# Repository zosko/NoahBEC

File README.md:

# NoahBEC
Buck convertor 12V to 5V 3A for servos.

## Scheme

Board | Preview 
-----|-----
|

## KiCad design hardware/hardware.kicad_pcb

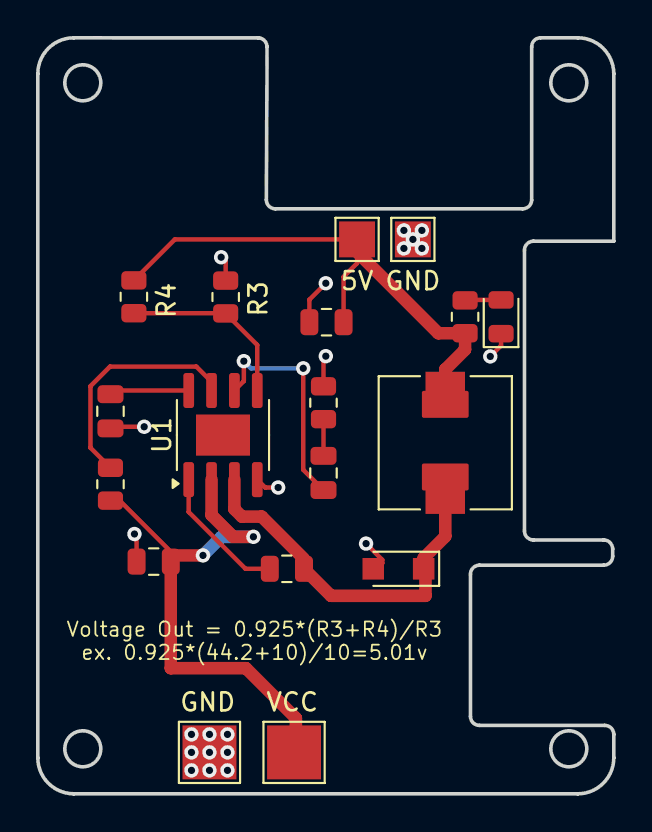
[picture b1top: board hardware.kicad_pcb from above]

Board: 2 copper layers, 32.0 x 42.0 mm, 18 parts (0 on the bottom side), 11 nets.

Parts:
5V: 5V OUTPUT; TestPoint_Pad_2.0x2.0mm
C1: 100nF; C_0805_2012Metric
C2: 3.9nF; C_0805_2012Metric
C4: 10nF; C_0805_2012Metric
C5, C6: 22uF; C_0805_2012Metric
D1: SS34; Nexperia_CFP3_SOD-123W
D2: LED; LED_0805_2012Metric
GND: GND; TestPoint_Pad_3.0x3.0mm
GND#2: GND OUTPUT; TestPoint_Pad_2.0x2.0mm
L1: 10uH; L_7.3x7.3_H3.5
R1: 6.8K; R_0805_2012Metric
R2: 100K; R_0805_2012Metric
R3: 10K; R_0805_2012Metric
R4: 44.2K; R_0805_2012Metric
R5: 300; R_0805_2012Metric
U1: MP2303ADN; SOIC-8-1EP_3.9x4.9mm_P1.27mm_EP2.29x3mm
VCC: VCC; TestPoint_Pad_3.0x3.0mm

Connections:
5V: 5V.1, C5.2, L1.1, R4.1, R5.2
GND: C1.1, C5.1, C6.1, D1.2 (A), D2.1 (K), GND.1, GND#2.1, R1.1, R3.1, U1.4 (GND)
unnamed: C2.1, R1.2
unnamed: C4.1, D1.1 (K), L1.2, U1.3 (SW)
unnamed: D2.2 (A), R5.1
unnamed: C6.2, R2.1, U1.2 (IN), VCC.1
unnamed: C4.2, U1.1 (BS)
unnamed: C2.2, U1.6 (COMP)
unnamed: R2.2, U1.7 (EN)
unnamed: R3.2, R4.2, U1.5 (FB)
unnamed: C1.2, U1.8 (SS)

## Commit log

2022-12-12 improve version
2022-12-19 rev1
2023-11-30 remove old project
2023-11-30 add noah bec rev 1
2023-11-30 add new images
2023-12-04 add 3d model for inductor
2023-12-04 replace pcb image
2024-03-05 rev1 project
2024-03-05 rev1 images
2025-07-31 update rev2
2025-08-01 gerber files re-create
